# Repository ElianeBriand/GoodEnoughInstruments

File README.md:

PCB designs &amp; software for DIY instrumentation and random stuffs.

No guarantee whatsoever of fitness for purpose.

# Description of projects

- USB_JTAG: a 3.3v USB-to-JTAG board based on a FTDI chip. Can also be used in USB-to-Serial and other FTDI-supported mode. Finished and working

- Watercooling4cats: Formally a miniature air/floor cooler for my cat (gets hot in the summer). Based on watercooling supplies, a stock CPU fan and a peltier. Can be used as the cooling system for a thermally controlled small enclosure (with temperature feedback) when the cat considers it unnecessary. Hardware is mostly done (a few bodge to be added to the current board file), firmware being written (FreeRTOS-based)

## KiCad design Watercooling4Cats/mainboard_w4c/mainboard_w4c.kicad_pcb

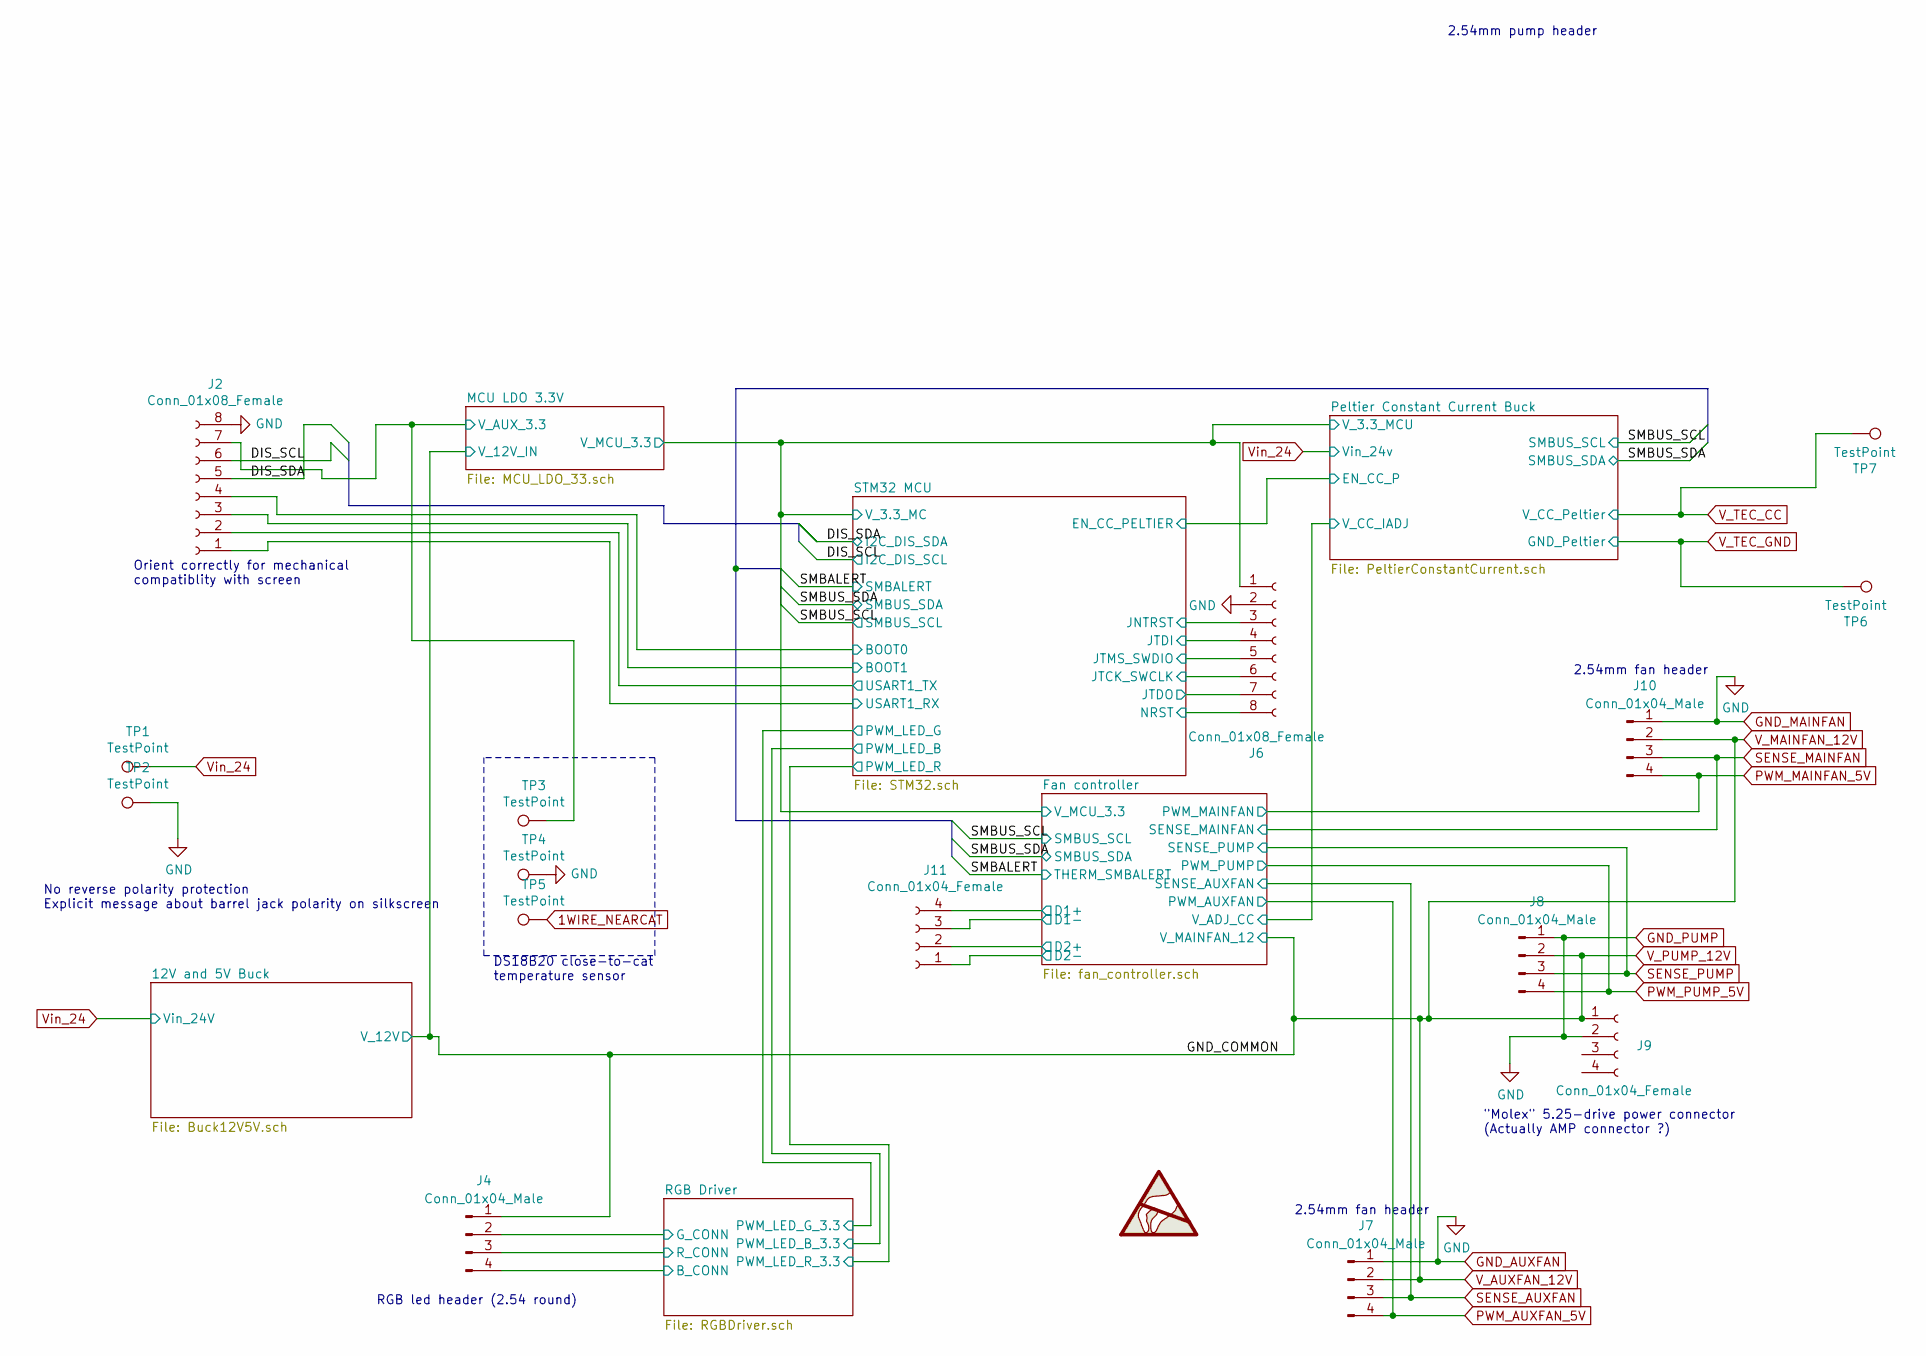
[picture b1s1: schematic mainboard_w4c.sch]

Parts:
J2, J6: Conn_01x08_Female; PinSocket_1x08_P2.54mm_Vertical
J4, J7, J8, J10: Conn_01x04_Male; PinHeader_1x04_P2.54mm_Vertical
J9: Conn_01x04_Female; PinHeader_1x04_P2.54mm_Vertical
J11: Conn_01x04_Female; PinSocket_1x04_P2.54mm_Vertical
SYM1: SYM_ESD_Large; Symbol_ESD-Logo_CopperTop
TP1, TP2: TestPoint; TestPoint_Loop_D3.80mm_Drill2.0mm
TP3, TP4, TP5: TestPoint; TestPoint_Loop_D1.80mm_Drill1.0mm_Beaded
TP6, TP7: TestPoint; TestPoint_Loop_D3.80mm_Drill2.8mm

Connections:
1WIRE_NEARCAT: TP5.1; also elsewhere on the board
/DIS_SCL: J2.6; also elsewhere on the board
/DIS_SDA: J2.5; also elsewhere on the board
/Fan controller/D1+: J11.4; also elsewhere on the board
/Fan controller/D1-: J11.3; also elsewhere on the board
/Fan controller/D2+: J11.2; also elsewhere on the board
/Fan controller/D2-: J11.1; also elsewhere on the board
/RGB Driver/B_CONN: J4.4; also elsewhere on the board
/RGB Driver/G_CONN: J4.2; also elsewhere on the board
/RGB Driver/R_CONN: J4.3; also elsewhere on the board
/STM32 MCU/BOOT0: J2.4; also elsewhere on the board
/STM32 MCU/BOOT1: J2.3; also elsewhere on the board
/STM32 MCU/JNTRST: J6.3; also elsewhere on the board
/STM32 MCU/JTCK_SWCLK: J6.6; also elsewhere on the board
/STM32 MCU/JTDI: J6.4; also elsewhere on the board
/STM32 MCU/JTDO: J6.7; also elsewhere on the board
/STM32 MCU/JTMS_SWDIO: J6.5; also elsewhere on the board
/STM32 MCU/NRST: J6.8; also elsewhere on the board
/STM32 MCU/USART1_RX: J2.1; also elsewhere on the board
/STM32 MCU/USART1_TX: J2.2; also elsewhere on the board
/STM32 MCU/V_3.3_MC: J2.7, J6.1, TP3.1; also elsewhere on the board
GND_AUXFAN: J2.8, J6.2, J7.1, J8.1, J9.2, J10.1, TP2.1, TP4.1, TP6.1; also elsewhere on the board
PWM_AUXFAN_5V: J7.4; also elsewhere on the board
PWM_MAINFAN_5V: J10.4; also elsewhere on the board
PWM_PUMP_5V: J8.4; also elsewhere on the board
SENSE_AUXFAN: J7.3; also elsewhere on the board
SENSE_MAINFAN: J10.3; also elsewhere on the board
SENSE_PUMP: J8.3; also elsewhere on the board
V_AUXFAN_12V: J4.1, J7.2, J8.2, J9.1, J10.2; also elsewhere on the board
V_TEC_CC: TP7.1; also elsewhere on the board
Vin_24: TP1.1; also elsewhere on the board

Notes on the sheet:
2.54mm fan header
No reverse polarity protection Explicit message about barrel jack polarity on silkscreen
2.54mm pump header
"Molex" 5.25-drive power connector (Actually AMP connector ?)
RGB led header (2.54 round)
Orient correctly for mechanical compatiblity with screen
DS18B20 close-to-cat temperature sensor

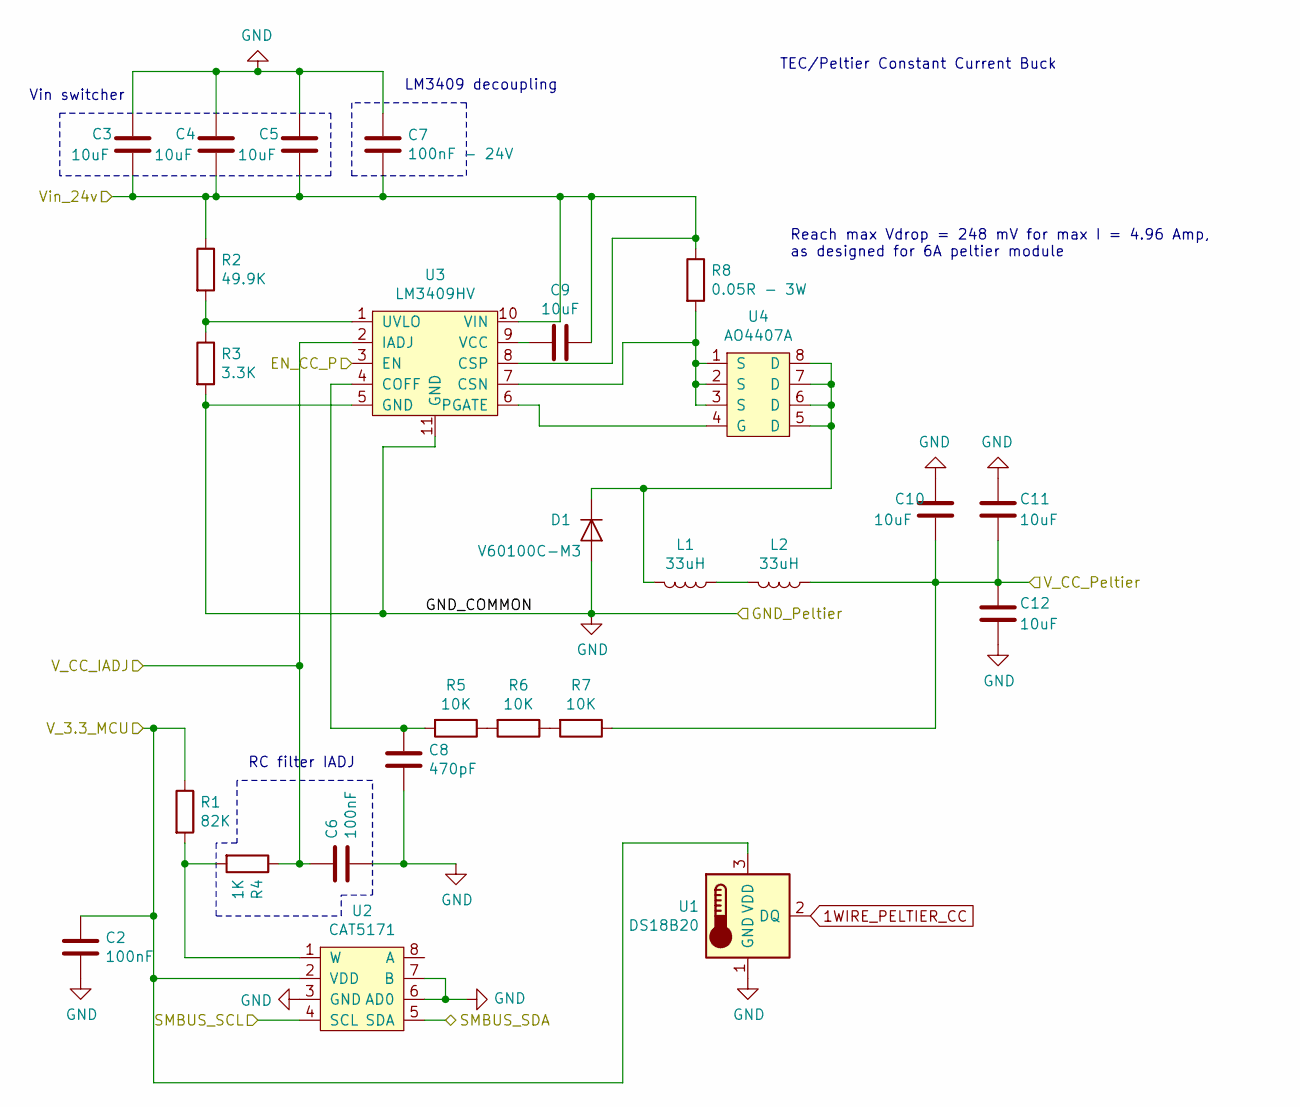
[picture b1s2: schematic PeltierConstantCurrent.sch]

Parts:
C2, C6: 100nF; C_0402_1005Metric
C3, C4, C5, C9, C10, C11, C12: 10uF; C_1206_3216Metric
C7: 100nF - 24V; C_0603_1608Metric
C8: 470pF; C_0603_1608Metric
D1: V60100C-M3; TO-220-3_Horizontal_TabUp
L1, L2: 33uH; L_Toroid_Vertical_L16.4mm_W7.6mm_P6.60mm_Vishay_TJ3
R1: 82K; R_0603_1608Metric
R2: 49.9K; R_0805_2012Metric
R3: 3.3K; R_0805_2012Metric
R4: 1K; R_0603_1608Metric
R5, R6, R7: 10K; R_1206_3216Metric
R8: 0.05R - 3W; R_2512_6332Metric
U1: DS18B20; TO-92_Inline
U2: CAT5171; SOT-23-8
U3: LM3409HV; MSOP-10-1EP_3x3mm_P0.5mm_EP1.68x1.88mm
U4: AO4407A; SOIC-8_3.9x4.9mm_P1.27mm

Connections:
1WIRE_PELTIER_CC: U1.2 (DQ); also elsewhere on the board
/Fan controller/V_ADJ_CC: C6.1, R4.1, U3.2 (IADJ); also elsewhere on the board
/Peltier Constant Current Buck/EN_CC_P: U3.3 (EN); also elsewhere on the board
/SMBUS_SCL: U2.4 (SCL); also elsewhere on the board
/SMBUS_SDA: U2.5 (SDA); also elsewhere on the board
/STM32 MCU/V_3.3_MC: C2.1, R1.1, U1.3 (VDD), U2.2 (VDD); also elsewhere on the board
GND_AUXFAN: C2.2, C3.2, C4.2, C5.2, C6.2, C7.2, C8.2, C10.2, C11.2, C12.1, D1.2 (A), R3.2, U1.1 (GND), U2.3 (GND), U2.6 (AD0), U2.7 (B), U3.5 (GND), U3.11 (GND); also elsewhere on the board
unnamed: C8.1, R5.2, U3.4 (COFF)
unnamed: C9.2, U3.9 (VCC)
unnamed: D1.1 (K), L1.2, U4.5 (D), U4.6 (D), U4.7 (D), U4.8 (D)
unnamed: L1.1, L2.2
unnamed: R1.2, R4.2, U2.1 (W)
unnamed: R2.2, R3.1, U3.1 (UVLO)
unnamed: R5.1, R6.2
unnamed: R6.1, R7.2
unnamed: R8.2, U3.7 (CSN), U4.1 (S), U4.2 (S), U4.3 (S)
unnamed: U3.6 (PGATE), U4.4 (G)
V_TEC_CC: C10.1, C11.1, C12.2, L2.1, R7.1; also elsewhere on the board
Vin_24: C3.1, C4.1, C5.1, C7.1, C9.1, R2.1, R8.1, U3.8 (CSP), U3.10 (VIN); also elsewhere on the board

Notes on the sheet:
TEC/Peltier Constant Current Buck
Reach max Vdrop = 248 mV for max I = 4.96 Amp, as designed for 6A peltier module
Vin switcher
LM3409 decoupling
RC filter IADJ

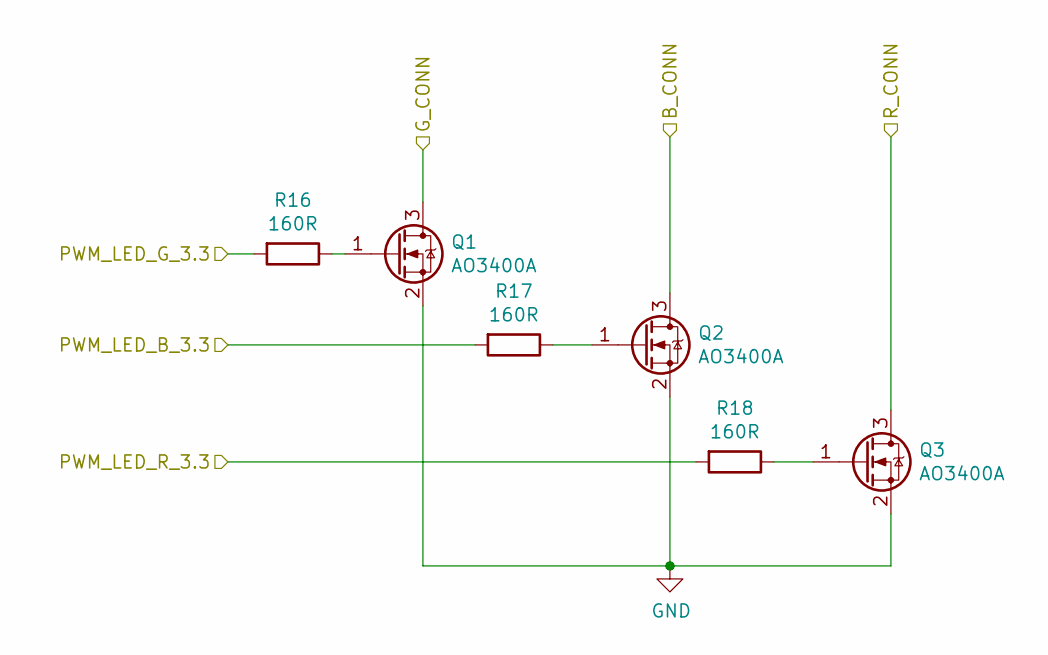
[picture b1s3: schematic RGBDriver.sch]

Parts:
Q1, Q2, Q3: AO3400A; SOT-23
R16, R17, R18: 160R; R_0603_1608Metric

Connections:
/RGB Driver/B_CONN: Q2.3 (D); also elsewhere on the board
/RGB Driver/G_CONN: Q1.3 (D); also elsewhere on the board
/RGB Driver/R_CONN: Q3.3 (D); also elsewhere on the board
/STM32 MCU/PWM_LED_B: R17.2; also elsewhere on the board
/STM32 MCU/PWM_LED_G: R16.2; also elsewhere on the board
/STM32 MCU/PWM_LED_R: R18.2; also elsewhere on the board
GND_AUXFAN: Q1.2 (S), Q2.2 (S), Q3.2 (S); also elsewhere on the board
unnamed: Q1.1 (G), R16.1
unnamed: Q2.1 (G), R17.1
unnamed: Q3.1 (G), R18.1

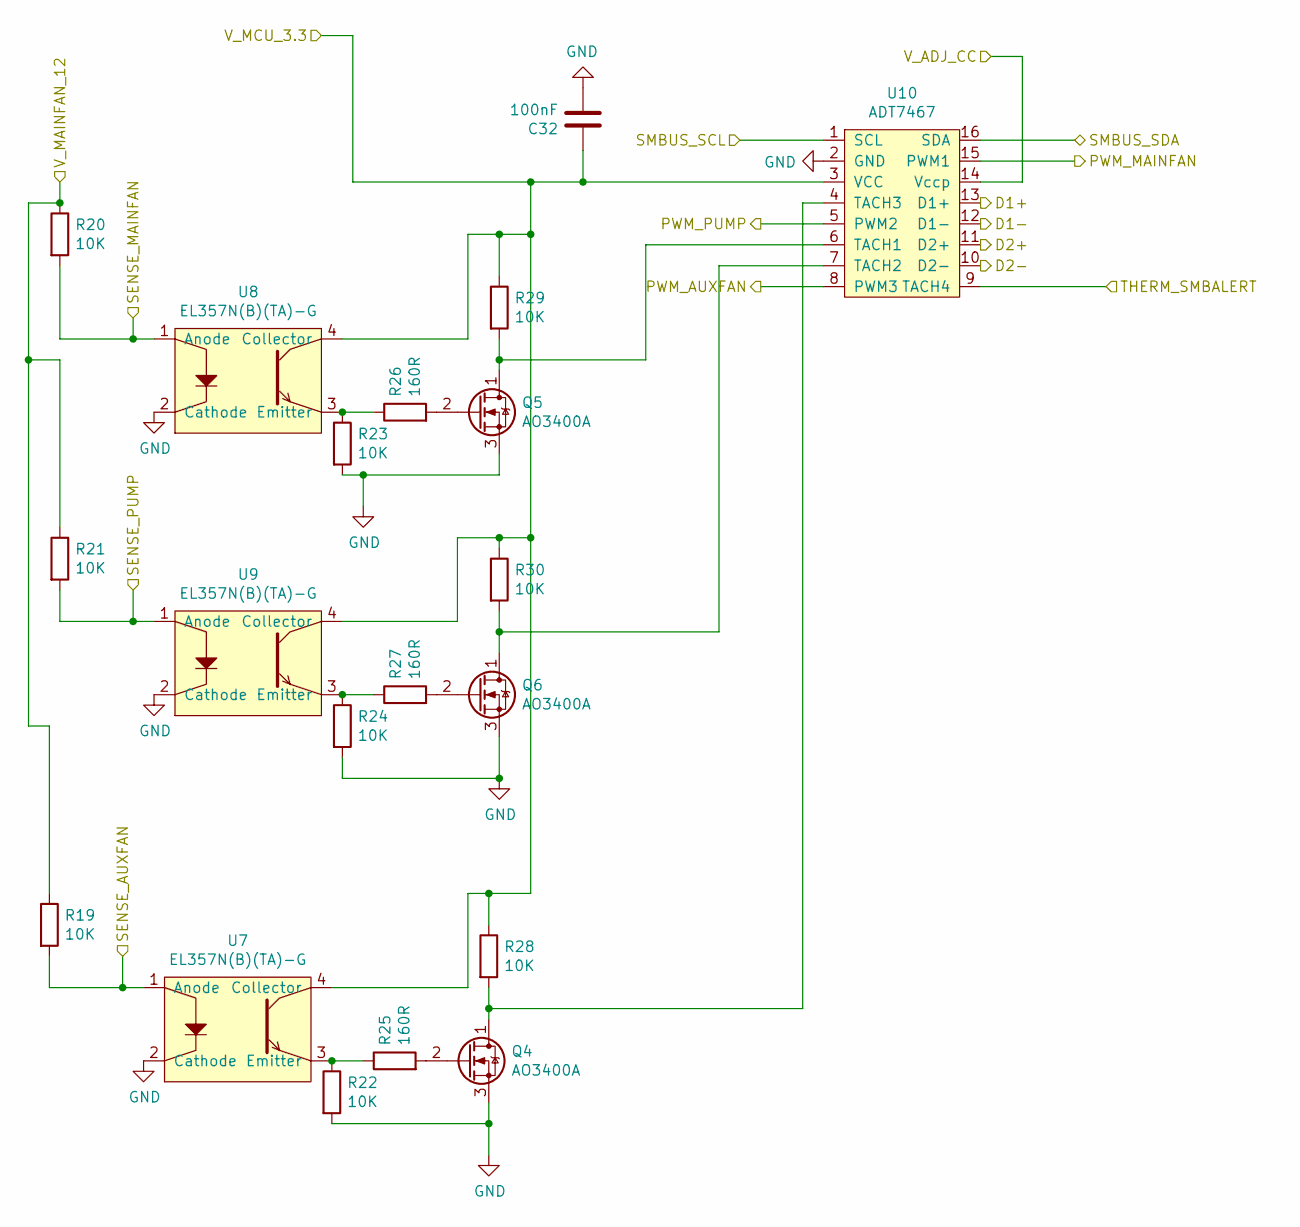
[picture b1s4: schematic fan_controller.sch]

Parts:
C32: 100nF; C_0402_1005Metric
Q4, Q5, Q6: AO3400A; SOT-23
R19, R20, R21: 10K; R_1206_3216Metric
R22, R23, R24, R28, R29, R30: 10K; R_0402_1005Metric
R25, R26, R27: 160R; R_0603_1608Metric
U7, U8, U9: EL357N(B)(TA)-G; SO-4_4.4x4.3mm_P2.54mm
U10: ADT7467; QSOP-16_3.9x4.9mm_P0.635mm

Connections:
/Fan controller/D1+: U10.13 (D1+); also elsewhere on the board
/Fan controller/D1-: U10.12 (D1-); also elsewhere on the board
/Fan controller/D2+: U10.11 (D2+); also elsewhere on the board
/Fan controller/D2-: U10.10 (D2-); also elsewhere on the board
/Fan controller/V_ADJ_CC: U10.14 (Vccp); also elsewhere on the board
/SMBALERT: U10.9 (TACH4); also elsewhere on the board
/SMBUS_SCL: U10.1 (SCL); also elsewhere on the board
/SMBUS_SDA: U10.16 (SDA); also elsewhere on the board
/STM32 MCU/V_3.3_MC: C32.1, R28.1, R29.1, R30.1, U7.4 (Collector), U8.4 (Collector), U9.4 (Collector), U10.3 (VCC); also elsewhere on the board
GND_AUXFAN: C32.2, Q4.3 (S), Q5.3 (S), Q6.3 (S), R22.2, R23.2, R24.2, U7.2 (Cathode), U8.2 (Cathode), U9.2 (Cathode), U10.2 (GND); also elsewhere on the board
unnamed: Q4.1 (D), R28.2, U10.4 (TACH3)
unnamed: Q4.2 (G), R25.2
unnamed: Q5.1 (D), R29.2, U10.6 (TACH1)
unnamed: Q5.2 (G), R26.2
unnamed: Q6.1 (D), R30.2, U10.7 (TACH2)
unnamed: Q6.2 (G), R27.2
unnamed: R22.1, R25.1, U7.3 (Emitter)
unnamed: R23.1, R26.1, U8.3 (Emitter)
unnamed: R24.1, R27.1, U9.3 (Emitter)
PWM_AUXFAN_5V: U10.8 (PWM3); also elsewhere on the board
PWM_MAINFAN_5V: U10.15 (PWM1); also elsewhere on the board
PWM_PUMP_5V: U10.5 (PWM2); also elsewhere on the board
SENSE_AUXFAN: R19.2, U7.1 (Anode); also elsewhere on the board
SENSE_MAINFAN: R20.2, U8.1 (Anode); also elsewhere on the board
SENSE_PUMP: R21.2, U9.1 (Anode); also elsewhere on the board
V_AUXFAN_12V: R19.1, R20.1, R21.1; also elsewhere on the board

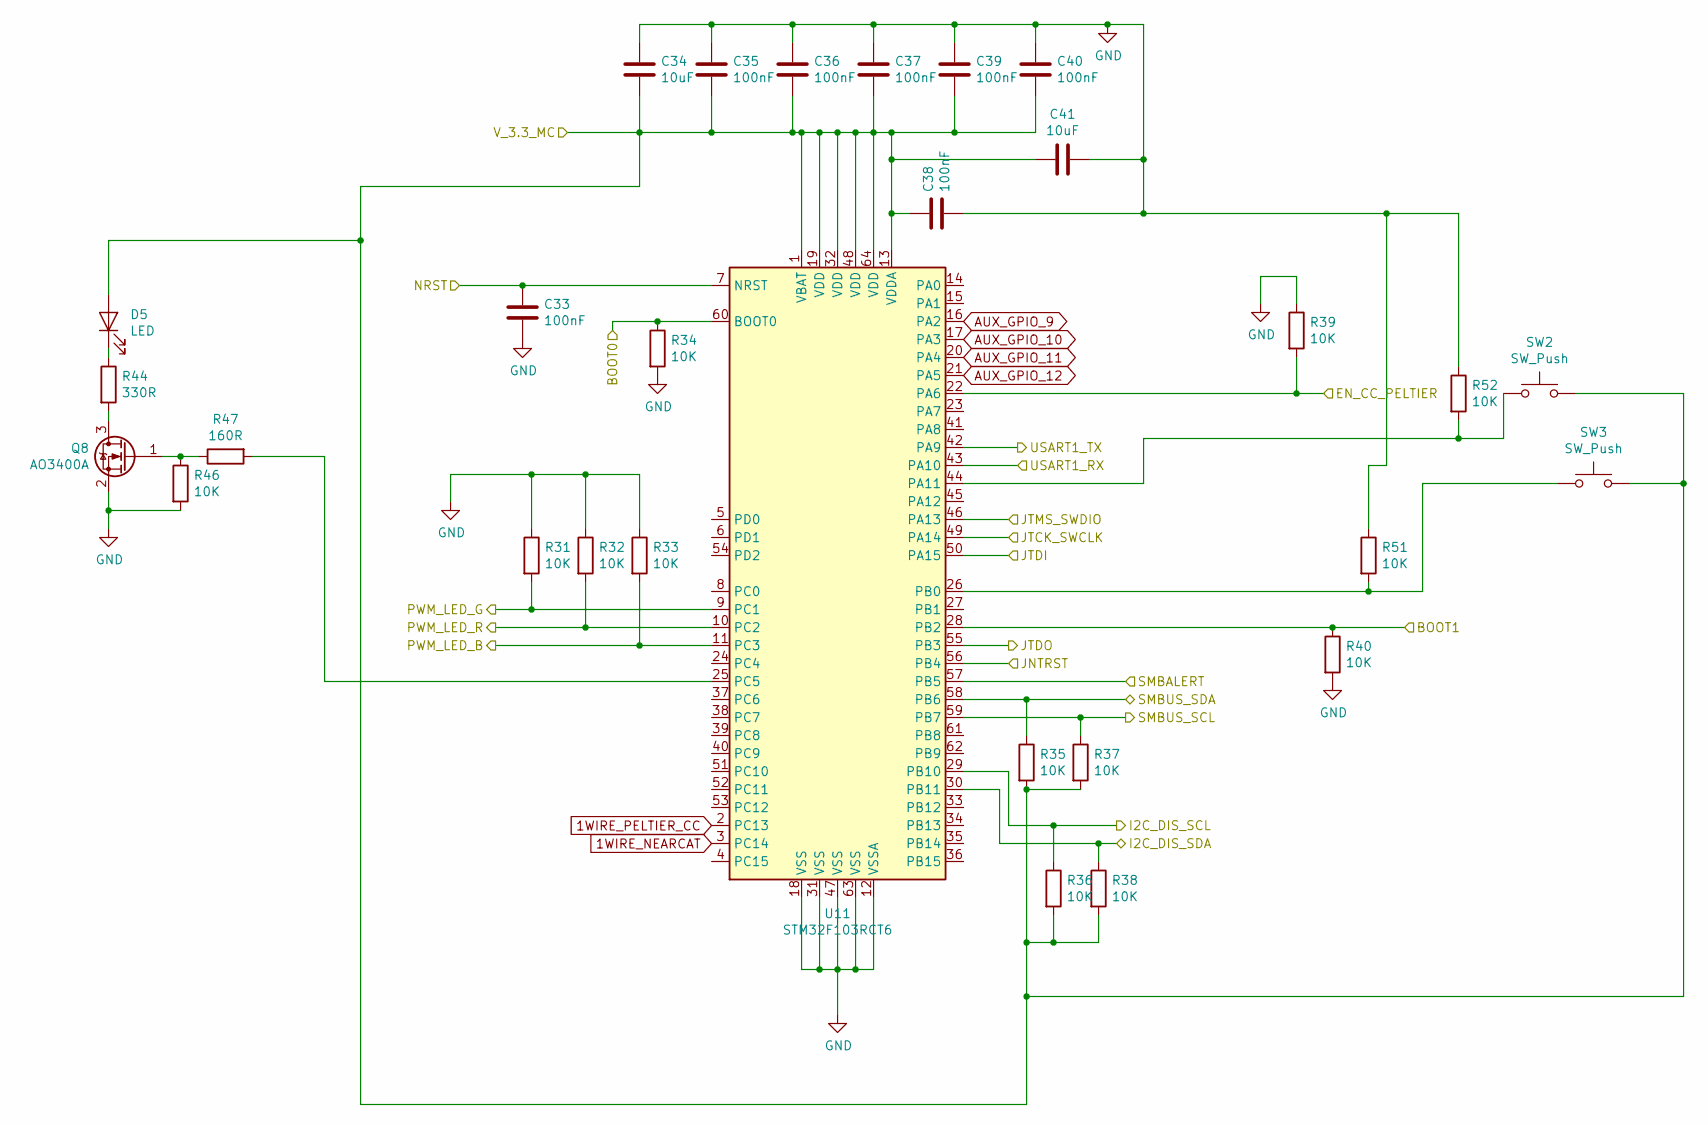
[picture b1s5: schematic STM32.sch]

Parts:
C33, C35, C36, C37, C38, C39, C40: 100nF; C_0402_1005Metric
C34, C41: 10uF; C_1206_3216Metric
D5: LED; LED_0603_1608Metric
Q8: AO3400A; SOT-23
R31, R32, R33, R34, R35, R36, R37, R38, R39, R40, R46, R51, R52: 10K; R_0402_1005Metric
R44: 330R; R_0402_1005Metric
R47: 160R; R_0603_1608Metric
SW2, SW3: SW_Push; SW_PUSH_6mm_H5mm
U11: STM32F103RCT6; LQFP-64_10x10mm_P0.5mm

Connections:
1WIRE_NEARCAT: U11.3 (PC14); also elsewhere on the board
1WIRE_PELTIER_CC: U11.2 (PC13); also elsewhere on the board
/DIS_SCL: R36.1, U11.29 (PB10); also elsewhere on the board
/DIS_SDA: R38.1, U11.30 (PB11); also elsewhere on the board
/Peltier Constant Current Buck/EN_CC_P: R39.2, U11.22 (PA6); also elsewhere on the board
/SMBALERT: U11.57 (PB5); also elsewhere on the board
/SMBUS_SCL: R37.1, U11.59 (PB7); also elsewhere on the board
/SMBUS_SDA: R35.1, U11.58 (PB6); also elsewhere on the board
/STM32 MCU/BOOT0: R34.1, U11.60 (BOOT0); also elsewhere on the board
/STM32 MCU/BOOT1: R40.1, U11.28 (PB2); also elsewhere on the board
/STM32 MCU/JNTRST: U11.56 (PB4); also elsewhere on the board
/STM32 MCU/JTCK_SWCLK: U11.49 (PA14); also elsewhere on the board
/STM32 MCU/JTDI: U11.50 (PA15); also elsewhere on the board
/STM32 MCU/JTDO: U11.55 (PB3); also elsewhere on the board
/STM32 MCU/JTMS_SWDIO: U11.46 (PA13); also elsewhere on the board
/STM32 MCU/NRST: C33.1, U11.7 (NRST); also elsewhere on the board
/STM32 MCU/PWM_LED_B: R33.2, U11.11 (PC3); also elsewhere on the board
/STM32 MCU/PWM_LED_G: R31.2, U11.9 (PC1); also elsewhere on the board
/STM32 MCU/PWM_LED_R: R32.2, U11.10 (PC2); also elsewhere on the board
/STM32 MCU/USART1_RX: U11.43 (PA10); also elsewhere on the board
/STM32 MCU/USART1_TX: U11.42 (PA9); also elsewhere on the board
/STM32 MCU/V_3.3_MC: C34.2, C35.2, C36.2, C37.2, C38.1, C39.2, C40.2, C41.2, D5.2 (A), R35.2, R36.2, R37.2, R38.2, SW2.2, SW3.2, U11.1 (VBAT), U11.13 (VDDA), U11.19 (VDD), U11.32 (VDD), U11.48 (VDD), U11.64 (VDD); also elsewhere on the board
AUX_GPIO_9: U11.16 (PA2)
AUX_GPIO_10: U11.17 (PA3)
AUX_GPIO_11: U11.20 (PA4)
AUX_GPIO_12: U11.21 (PA5)
GND_AUXFAN: C33.2, C34.1, C35.1, C36.1, C37.1, C38.2, C39.1, C40.1, C41.1, Q8.2 (S), R31.1, R32.1, R33.1, R34.2, R39.1, R40.2, R46.2, R51.1, R52.1, U11.12 (VSSA), U11.18 (VSS), U11.31 (VSS), U11.47 (VSS), U11.63 (VSS); also elsewhere on the board
unnamed: D5.1 (K), R44.1
unnamed: Q8.1 (G), R46.1, R47.1
unnamed: Q8.3 (D), R44.2
unnamed: R47.2, U11.25 (PC5)
unnamed: R51.2, SW3.1, U11.26 (PB0)
unnamed: R52.2, SW2.1, U11.44 (PA11)

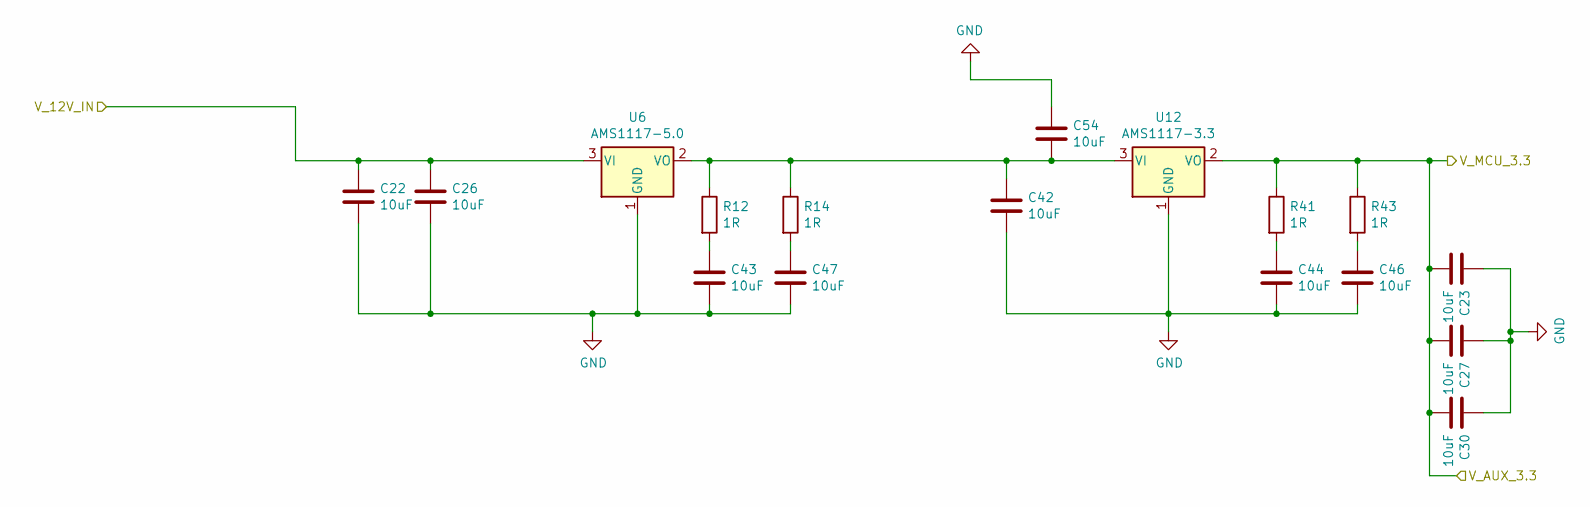
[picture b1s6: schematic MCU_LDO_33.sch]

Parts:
C22, C23, C26, C27, C30, C54: 10uF; C_1206_3216Metric
C42, C43, C44, C46, C47: 10uF; C_0805_2012Metric
R12, R14, R41, R43: 1R; R_1206_3216Metric
U6: AMS1117-5.0; SOT-223-3_TabPin2
U12: AMS1117-3.3; SOT-223-3_TabPin2

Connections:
/STM32 MCU/V_3.3_MC: C23.1, C27.1, C30.1, R41.1, R43.1, U12.2 (VO); also elsewhere on the board
GND_AUXFAN: C22.1, C23.2, C26.1, C27.2, C30.2, C42.2, C43.2, C44.2, C46.2, C47.2, C54.2, U6.1 (GND), U12.1 (GND); also elsewhere on the board
unnamed: C42.1, C54.1, R12.1, R14.1, U6.2 (VO), U12.3 (VI)
unnamed: C43.1, R12.2
unnamed: C44.1, R41.2
unnamed: C46.1, R43.2
unnamed: C47.1, R14.2
V_AUXFAN_12V: C22.2, C26.2, U6.3 (VI); also elsewhere on the board

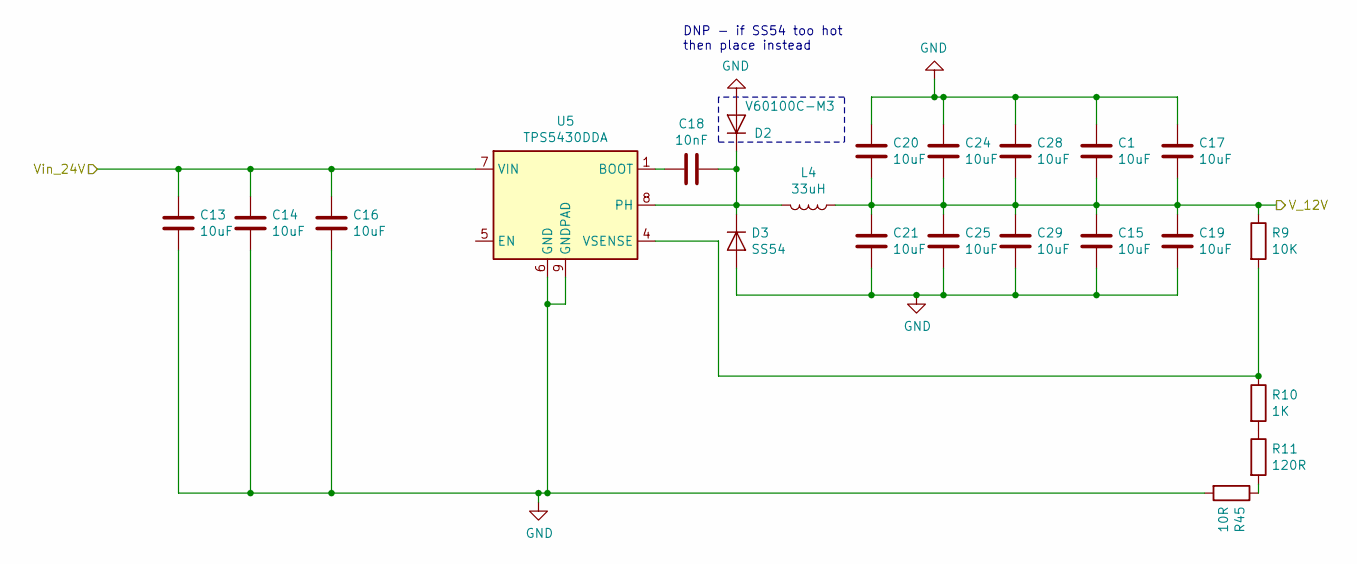
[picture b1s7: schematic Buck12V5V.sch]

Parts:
C1, C13, C14, C15, C16, C17, C19, C20, C21, C24, C25, C28, C29: 10uF; C_1206_3216Metric
C18: 10nF; C_0805_2012Metric
D2: V60100C-M3; TO-220-3_Horizontal_TabUp
D3: SS54; D_SMA
L4: 33uH; L_Toroid_Vertical_L16.4mm_W7.6mm_P6.60mm_Vishay_TJ3
R9: 10K; R_1206_3216Metric
R10: 1K; R_0603_1608Metric
R11: 120R; R_0603_1608Metric
R45: 10R; R_0603_1608Metric
U5: TPS5430DDA; TI_SO-PowerPAD-8

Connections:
GND_AUXFAN: C1.2, C13.1, C14.1, C15.1, C16.1, C17.2, C19.1, C20.2, C21.1, C24.2, C25.1, C28.2, C29.1, D2.2 (A), D3.2 (A), R45.2, U5.6 (GND), U5.9 (GNDPAD); also elsewhere on the board
unnamed: C18.1, D2.1 (K), D3.1 (K), L4.2, U5.8 (PH)
unnamed: C18.2, U5.1 (BOOT)
unnamed: R9.2, R10.1, U5.4 (VSENSE)
unnamed: R10.2, R11.1
unnamed: R11.2, R45.1
V_AUXFAN_12V: C1.1, C15.2, C17.1, C19.2, C20.1, C21.2, C24.1, C25.2, C28.1, C29.2, L4.1, R9.1; also elsewhere on the board
Vin_24: C13.2, C14.2, C16.2, U5.7 (VIN); also elsewhere on the board

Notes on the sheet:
DNP - if SS54 too hot then place instead

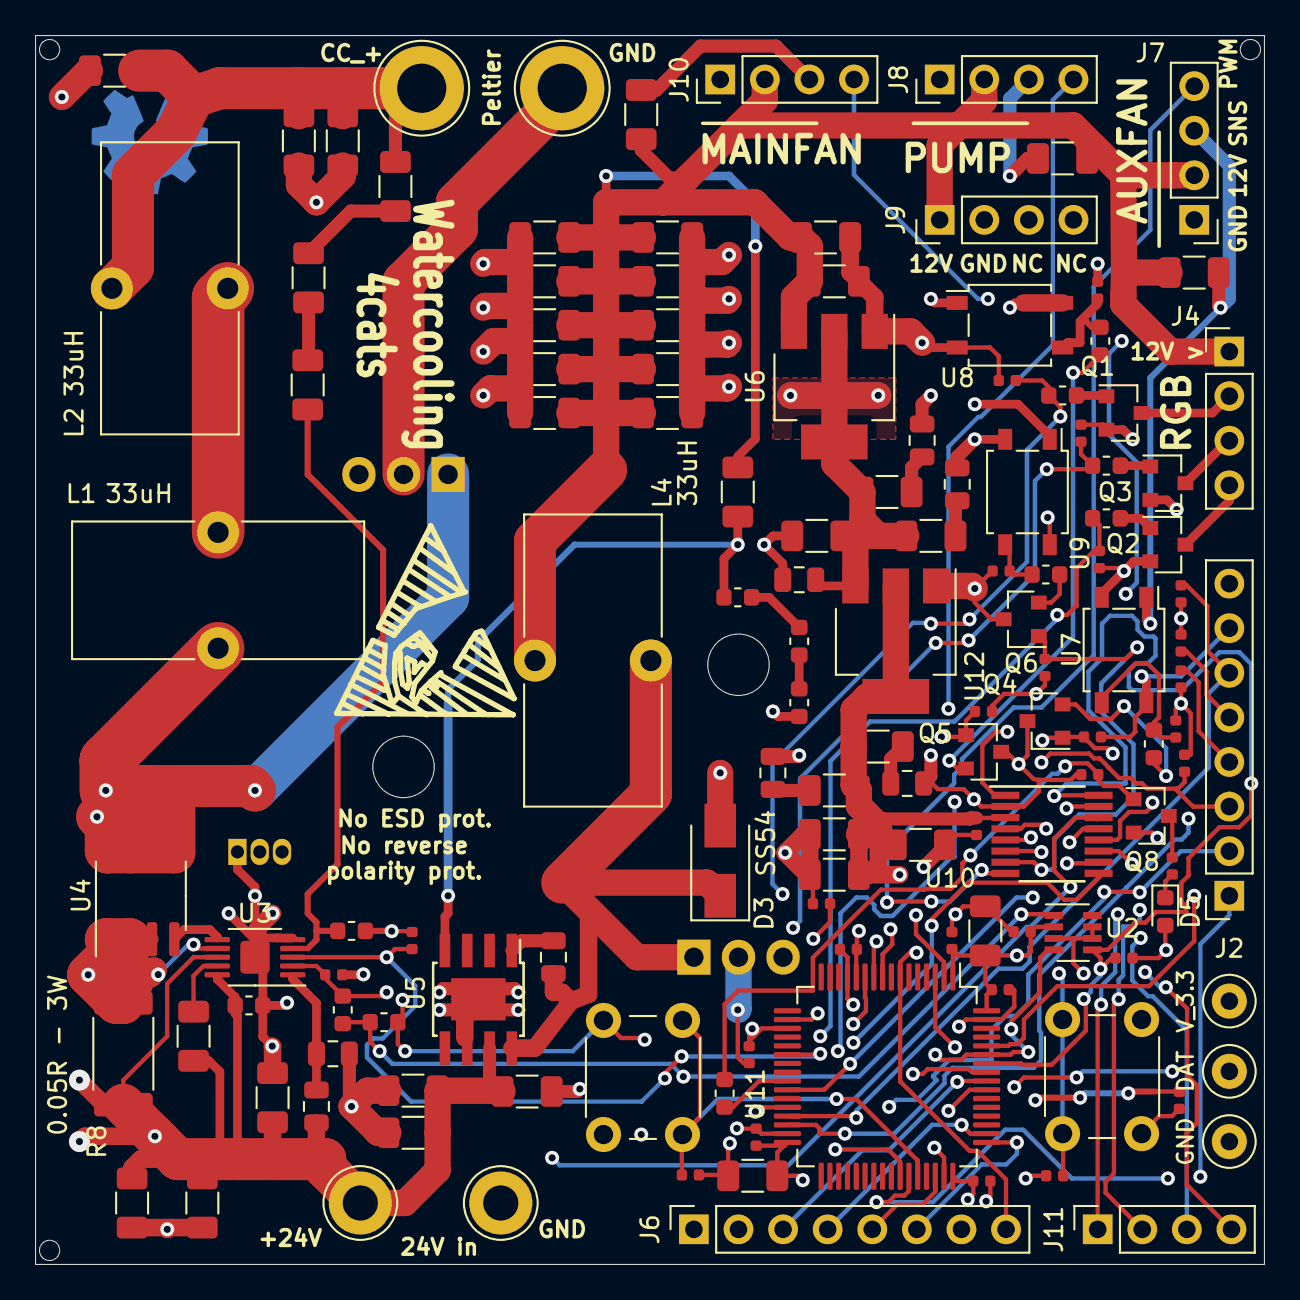
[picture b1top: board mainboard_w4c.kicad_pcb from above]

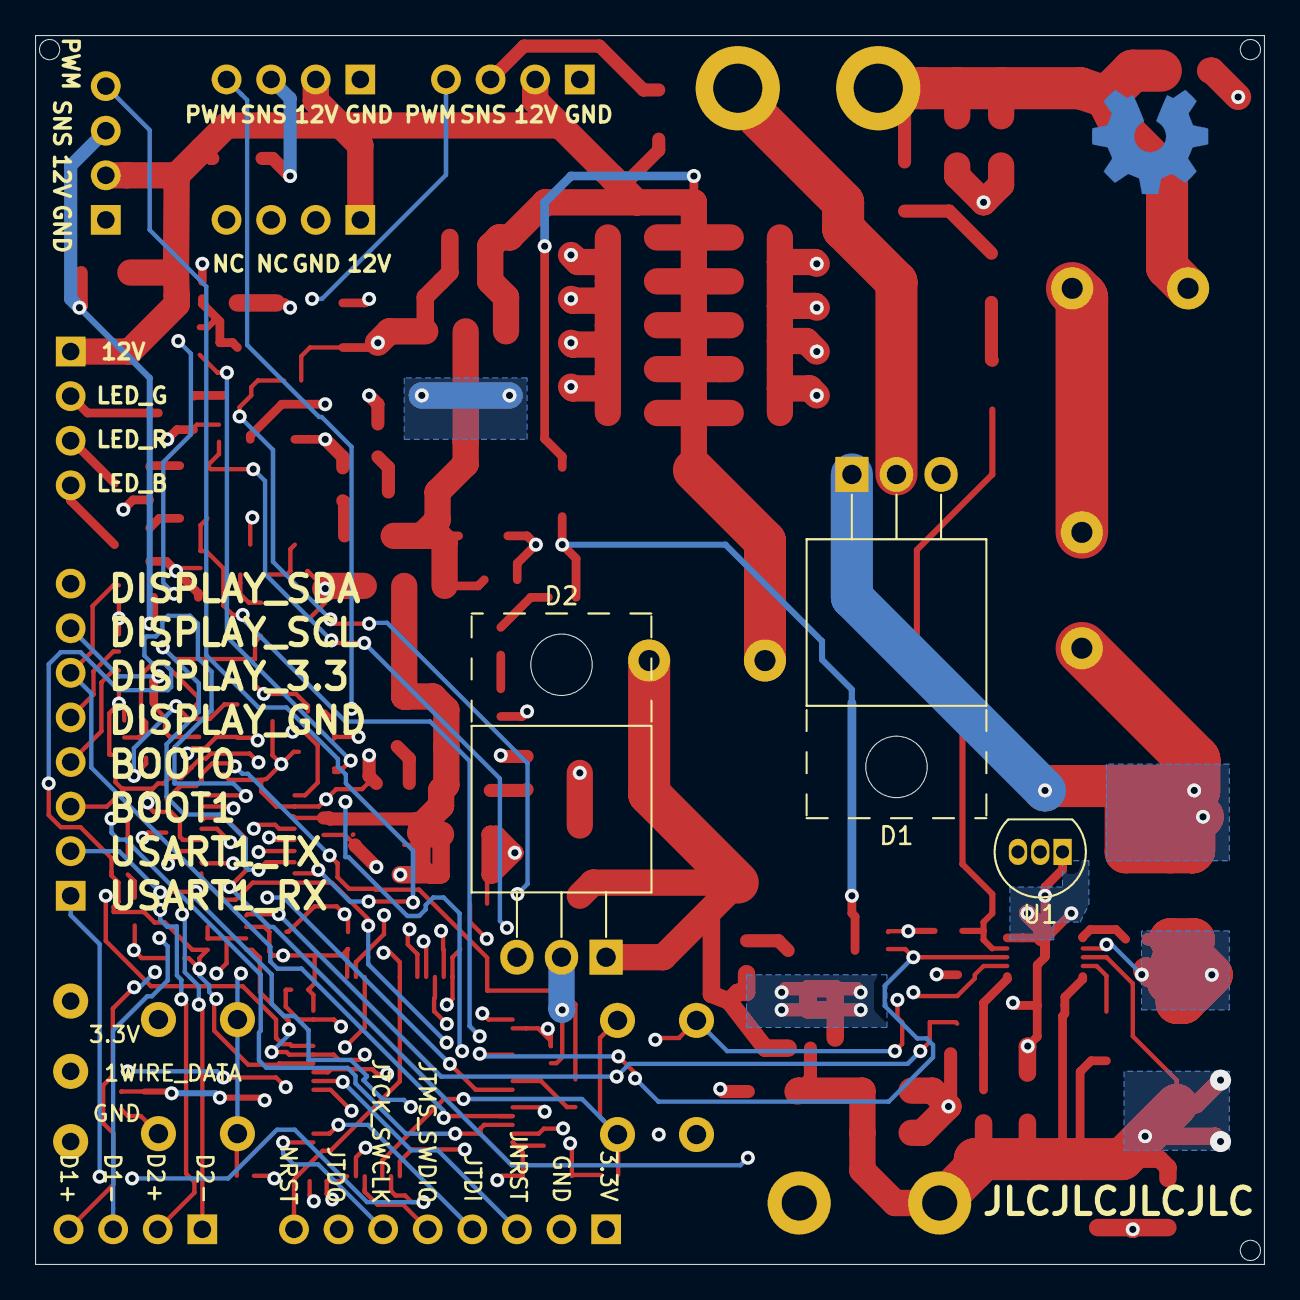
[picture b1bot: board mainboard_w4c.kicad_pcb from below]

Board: 4 copper layers, 70.0 x 70.0 mm, 136 parts (3 on the bottom side), 78 nets.

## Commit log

2019-11-09 USB JTAG
2019-12-23 USB-JTAG board picture
2020-09-04 Added Watercooling4cat project
